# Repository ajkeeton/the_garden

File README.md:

**Garden of the Wads**

Animation states:

0)
    - Glow or pulse near sensors. Occasional LED tracer
    - Wadsworth sighs
    - Venus closed

1)
    - *The initial state on startup*
    - Venus opens
    - The blue blob animation starts
    - Wadsworth breathes slowly, with pauses

2)
    - High energy tracers?
    - More colorful blobs?
    - Fast breathing?

3)
    - Mostly glowing white?
    - Rapid decay to state 2

TODOs:
- Doc PIR sensors and behavior
- The LED patterns are from old projects and need to be refactored
- Garden state updates from the Gardener are currently ignored

*Wadsworth*

*The Venus Hippy Trap*

*The Little Wads*

*Maki's Squishy Thing*

*The Garden server*

*NOTES*

For the Pi 4, need to disable wireless power saving:

```
echo iwconfig wlan0 power off > /etc/rc.local
```

The Arduino core: |The core: https://github.com/earlephilhower/arduino-pico

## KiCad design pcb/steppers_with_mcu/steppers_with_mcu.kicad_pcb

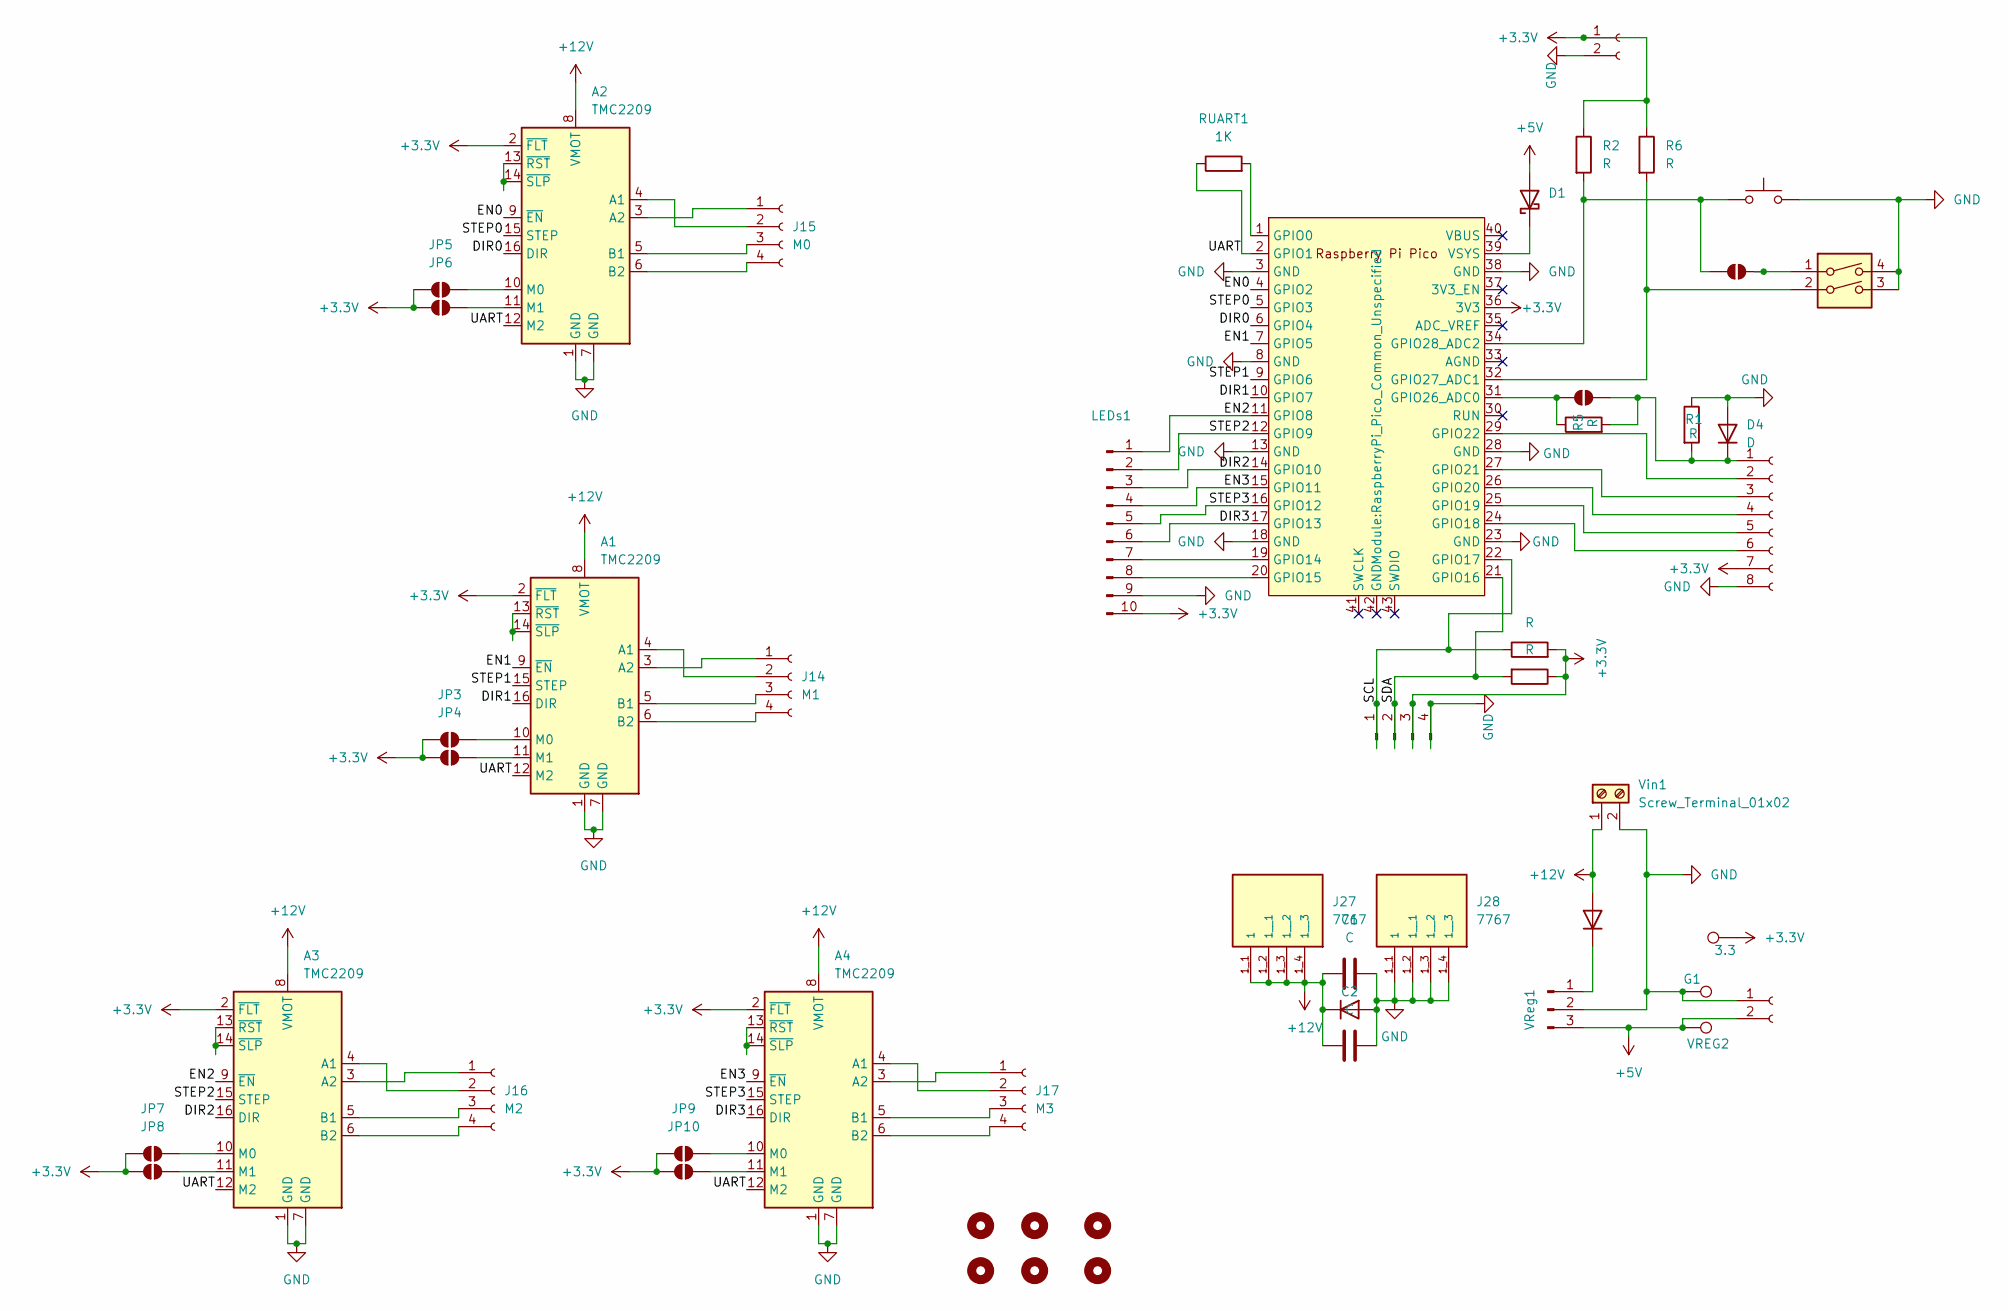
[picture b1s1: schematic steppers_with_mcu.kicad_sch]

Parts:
3.3: TestPoint; TestPoint_Pad_1.5x1.5mm
A1, A2, A3, A4: TMC2209; Pololu_Breakout-16_15.2x20.3mm
C1, C2: C; CP_Radial_D13.0mm_P5.00mm
D1: D_Schottky; D_DO-27_P15.24mm_Horizontal
D2, D3, D4: D; D_A-405_P10.16mm_Horizontal
G1: TestPoint; TestPoint_Pad_1.5x1.5mm
H1, H2, H3, H4, H5, H6: MountingHole; MountingHole_3.2mm_M3_ISO7380_Pad_TopBottom
I2C1: Conn_01x04_Pin; PinHeader_1x04_P2.54mm_Vertical
J2: Conn_01x08_Socket; PinHeader_1x08_P2.54mm_Vertical
J4, J5: Conn_01x02_Socket; PinHeader_1x02_P2.54mm_Vertical
J14: M1; PinHeader_1x04_P2.54mm_Vertical
J15: M0; PinHeader_1x04_P2.54mm_Vertical
J16: M2; PinHeader_1x04_P2.54mm_Vertical
J17: M3; PinHeader_1x04_P2.54mm_Vertical
J27, J28: 7767; KEYSTONE_7767; PARTREV B
JP1, JP2: SolderJumper_2_Open; SolderJumper-2_P1.3mm_Open_RoundedPad1.0x1.5mm
JP3, JP4, JP5, JP6, JP7, JP8, JP9, JP10: SolderJumper_2_Open; SolderJumper-2_P1.3mm_Open_Pad1.0x1.5mm
LEDs1: Conn_01x10_Pin; PinHeader_1x10_P2.54mm_Vertical
R1, R2, R3, R4, R5, R6: R; 1206
RUART1: 1K; 1206
SW1: SW_Push; SW_PUSH_6mm
SW2: SW_DIP_x02; SW_DIP_SPSTx02_Slide_6.7x6.64mm_W7.62mm_P2.54mm_LowProfile
U1: Pico; RaspberryPi_Pico_Common_Unspecified
VREG2: TestPoint; TestPoint_Pad_1.5x1.5mm
VReg1: Conn_01x03_Pin; PinHeader_1x03_P2.54mm_Vertical
Vin1: Screw_Terminal_01x02; TerminalBlock_Phoenix_MKDS-1,5-2_1x02_P5.00mm_Horizontal

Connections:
+3.3V: 3.3.1, A1.2 (~FLT), A2.2 (~FLT), A3.2 (~FLT), A4.2 (~FLT), I2C1.3, J2.7, J4.1, JP3.1 (A), JP4.1 (A), JP5.1 (A), JP6.1 (A), JP7.1 (A), JP8.1 (A), JP9.1 (A), JP10.1 (A), LEDs1.10, R2.1, R3.1, R4.2, R6.1, U1.36 (3V3)
+5V: D1.2 (A), J5.2, VREG2.1, VReg1.3
+12V: A1.8 (VMOT), A2.8 (VMOT), A3.8 (VMOT), A4.8 (VMOT), C1.1, C2.1, D2.2 (A), D3.1 (K), J27.1_1 (1), J27.1_2 (1__1), J27.1_3 (1__2), J27.1_4 (1__3), Vin1.1
/DIR0: A2.16 (DIR), U1.6 (GPIO4)
/DIR1: A1.16 (DIR), U1.10 (GPIO7)
/DIR2: A3.16 (DIR), LEDs1.3, U1.14 (GPIO10)
/DIR3: A4.16 (DIR), LEDs1.6, U1.17 (GPIO13)
/EN0: A2.9 (~EN), U1.4 (GPIO2)
/EN1: A1.9 (~EN), U1.7 (GPIO5)
/EN2: A3.9 (~EN), LEDs1.1, U1.11 (GPIO8)
/EN3: A4.9 (~EN), LEDs1.4, U1.15 (GPIO11)
/SCL: I2C1.1, R4.1, U1.22 (GPIO17)
/SDA: I2C1.2, R3.2, U1.21 (GPIO16)
/STEP0: A2.15 (STEP), U1.5 (GPIO3)
/STEP1: A1.15 (STEP), U1.9 (GPIO6)
/STEP2: A3.15 (STEP), LEDs1.2, U1.12 (GPIO9)
/STEP3: A4.15 (STEP), LEDs1.5, U1.16 (GPIO12)
/UART: A1.12 (M2), A2.12 (M2), A3.12 (M2), A4.12 (M2), RUART1.1, U1.2 (GPIO1)
GND: A1.1 (GND), A1.7 (GND), A2.1 (GND), A2.7 (GND), A3.1 (GND), A3.7 (GND), A4.1 (GND), A4.7 (GND), C1.2, C2.2, D3.2 (A), D4.2 (A), G1.1, I2C1.4, J2.8, J4.2, J5.1, J28.1_1 (1), J28.1_2 (1__1), J28.1_3 (1__2), J28.1_4 (1__3), LEDs1.9, R1.1, SW1.2, SW2.3, SW2.4, U1.3 (GND), U1.8 (GND), U1.13 (GND), U1.18 (GND), U1.23 (GND), U1.28 (GND), U1.38 (GND), VReg1.2, Vin1.2; also elsewhere on the board
unnamed: A1.4 (A1), J14.2
unnamed: A1.3 (A2), J14.1
unnamed: A1.5 (B1), J14.3
unnamed: A1.6 (B2), J14.4
unnamed: A1.10 (M0), JP3.2 (B)
unnamed: A1.11 (M1), JP4.2 (B)
unnamed: A1.13 (~RST), A1.14 (~SLP)
unnamed: A2.4 (A1), J15.2
unnamed: A2.3 (A2), J15.1
unnamed: A2.5 (B1), J15.3
unnamed: A2.6 (B2), J15.4
unnamed: A2.10 (M0), JP5.2 (B)
unnamed: A2.11 (M1), JP6.2 (B)
unnamed: A2.13 (~RST), A2.14 (~SLP)
unnamed: A3.4 (A1), J16.2
unnamed: A3.3 (A2), J16.1
unnamed: A3.5 (B1), J16.3
unnamed: A3.6 (B2), J16.4
unnamed: A3.10 (M0), JP7.2 (B)
unnamed: A3.11 (M1), JP8.2 (B)
unnamed: A3.13 (~RST), A3.14 (~SLP)
unnamed: A4.4 (A1), J17.2
unnamed: A4.3 (A2), J17.1
unnamed: A4.5 (B1), J17.3
unnamed: A4.6 (B2), J17.4
unnamed: A4.10 (M0), JP9.2 (B)
unnamed: A4.11 (M1), JP10.2 (B)
unnamed: A4.13 (~RST), A4.14 (~SLP)
unnamed: D1.1 (K), U1.39 (VSYS)
unnamed: D2.1 (K), VReg1.1
unnamed: D4.1 (K), J2.1, JP2.1 (A), R1.2, R5.2
unnamed: J2.2, U1.29 (GPIO22)
unnamed: J2.3, U1.27 (GPIO21)
unnamed: J2.4, U1.26 (GPIO20)
unnamed: J2.5, U1.25 (GPIO19)
unnamed: J2.6, U1.24 (GPIO18)
unnamed: JP1.1 (A), SW2.1
unnamed: JP1.2 (B), R2.2, SW1.1, U1.34 (GPIO28_ADC2)
unnamed: JP2.2 (B), R5.1, U1.31 (GPIO26_ADC0)
unnamed: LEDs1.7, U1.19 (GPIO14)
unnamed: LEDs1.8, U1.20 (GPIO15)
unnamed: RUART1.2, U1.1 (GPIO0)
unnamed: R6.2, SW2.2, U1.32 (GPIO27_ADC1)

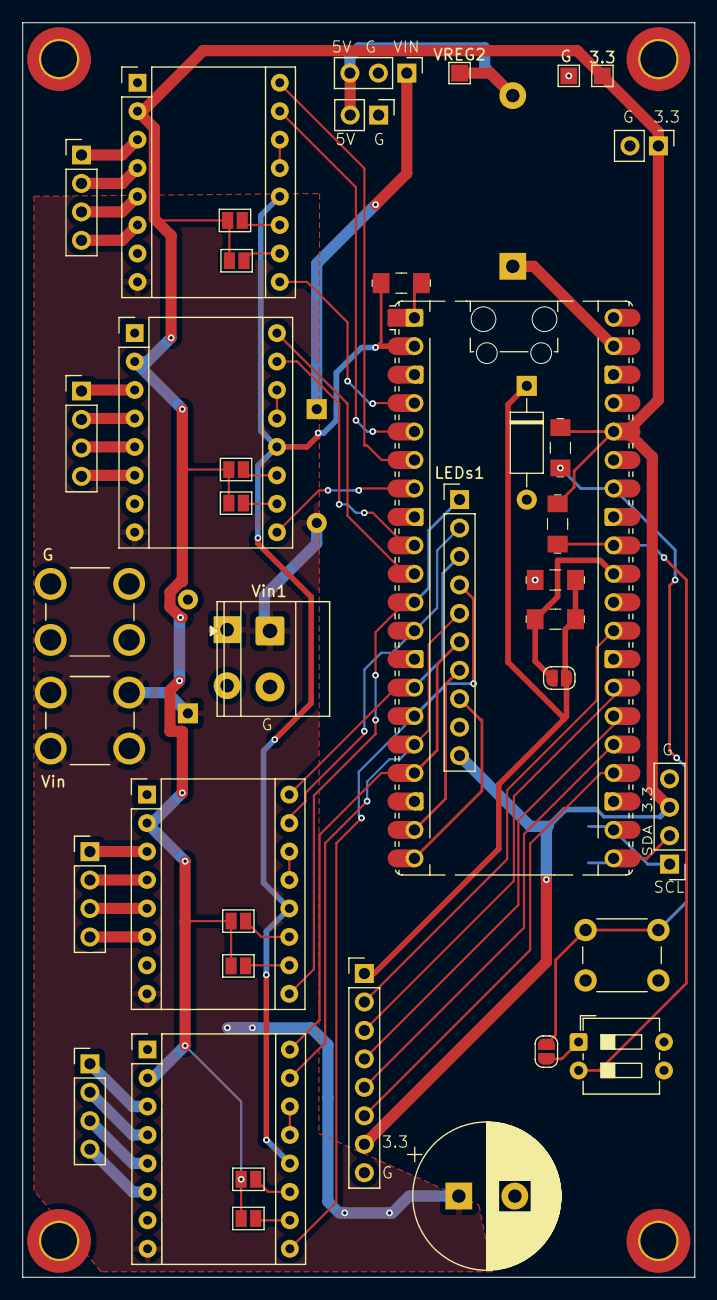
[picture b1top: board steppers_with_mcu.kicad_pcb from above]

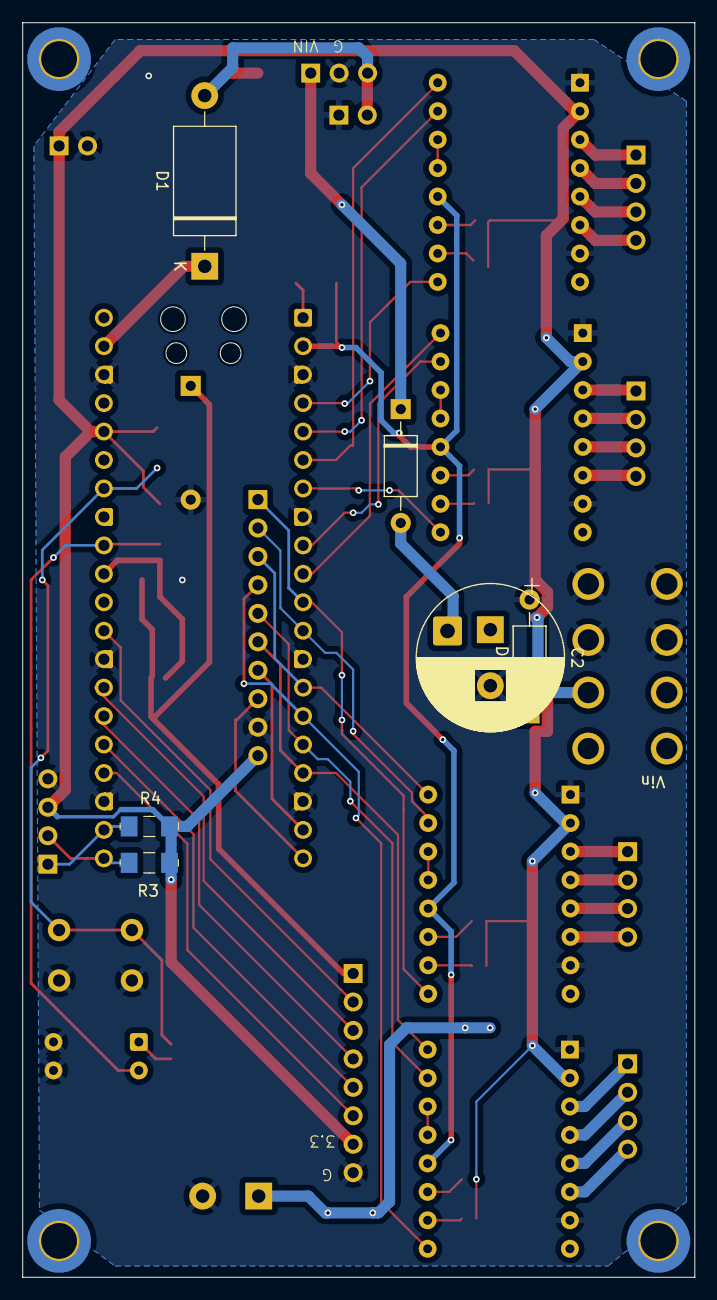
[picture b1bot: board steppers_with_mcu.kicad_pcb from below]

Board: 2 copper layers, 60.0 x 112.0 mm, 50 parts (6 on the bottom side), 62 nets.

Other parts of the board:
G: TestPoint; TestPoint_Pad_1.5x1.5mm

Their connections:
GND: G.1; also elsewhere on the board

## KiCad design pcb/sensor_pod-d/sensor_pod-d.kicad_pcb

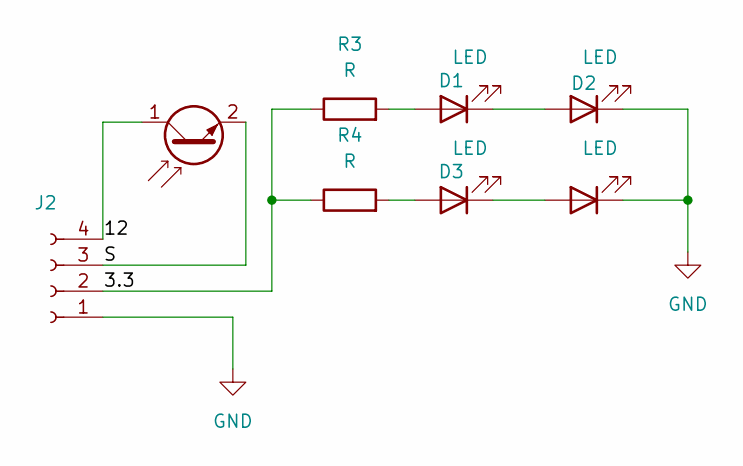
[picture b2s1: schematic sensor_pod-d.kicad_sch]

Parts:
D1, D2, D3, D4: LED; PinHeader_1x02_P2.54mm_Vertical
J2: Conn_01x04_Socket; PinHeader_1x04_P2.54mm_Vertical
Q2: Q_Photo_NPN; PinHeader_1x02_P2.54mm_Vertical
R3, R4: R; 1206

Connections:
/3.3: J2.2, R3.1, R4.1
/12: J2.4, Q2.1 (C)
/S: J2.3, Q2.2 (E)
GND: D2.1 (K), D4.1 (K), J2.1
unnamed: D1.2 (A), R3.2
unnamed: D1.1 (K), D2.2 (A)
unnamed: D3.2 (A), R4.2
unnamed: D3.1 (K), D4.2 (A)

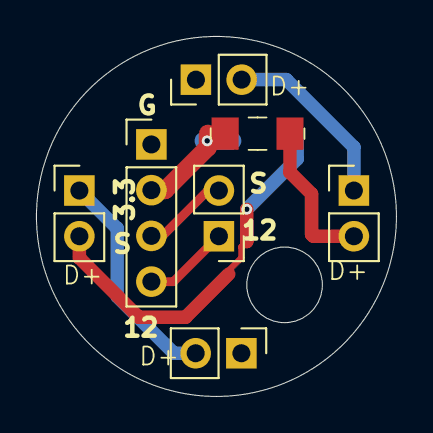
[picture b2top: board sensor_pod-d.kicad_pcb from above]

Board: 2 copper layers, 20.0 x 20.0 mm, 8 parts (1 on the bottom side), 8 nets.

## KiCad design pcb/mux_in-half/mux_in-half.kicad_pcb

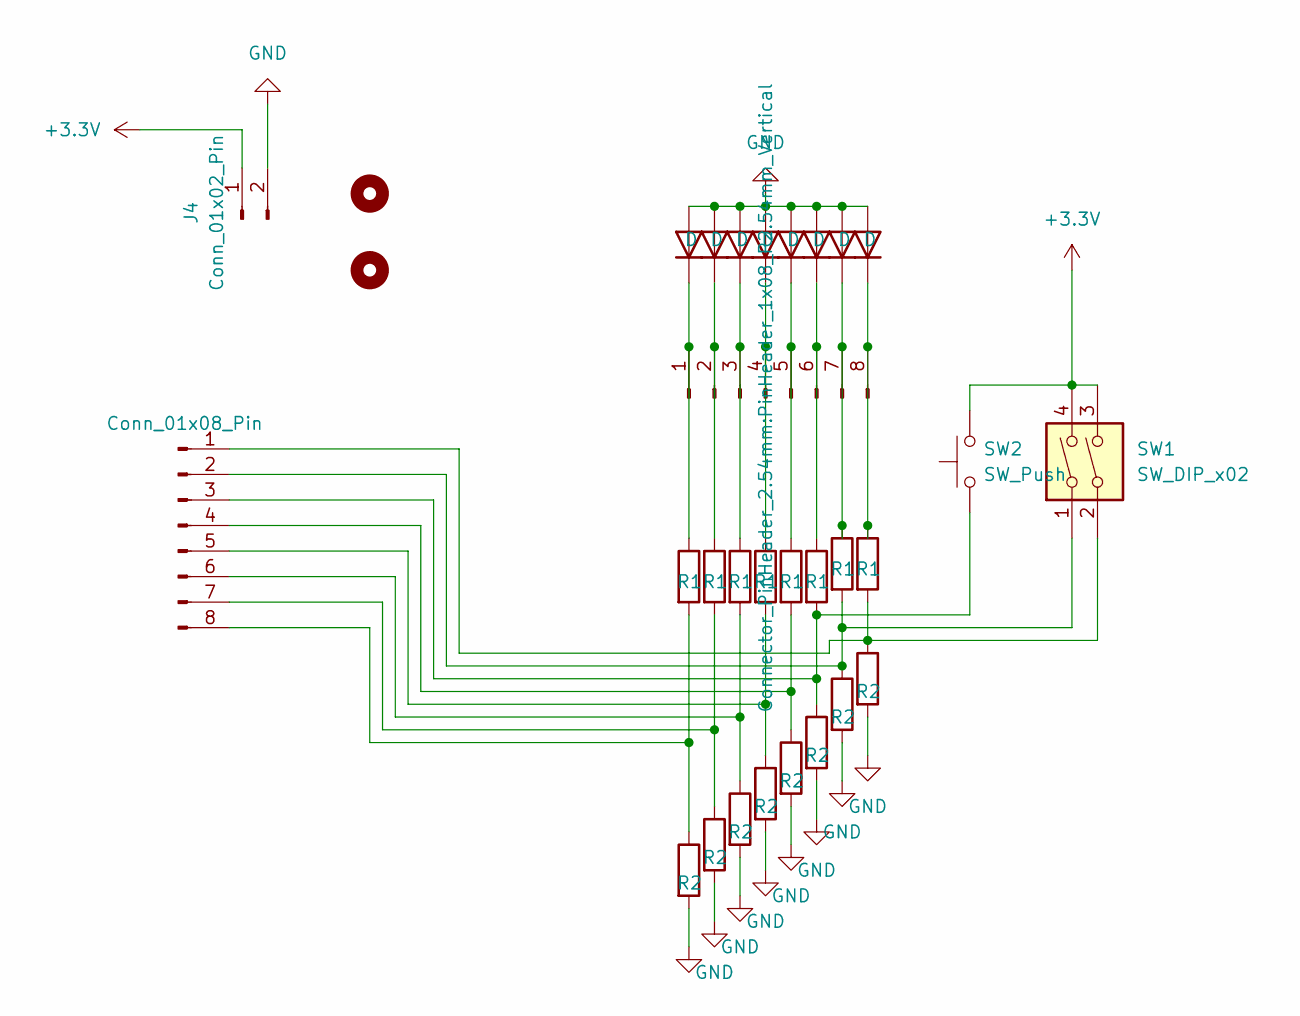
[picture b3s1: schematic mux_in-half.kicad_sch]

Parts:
D9, D10, D11, D12, D13, D14, D15, D16: D; D_SMF
H1, H2: MountingHole; MountingHole_2.5mm_Pad
J1, J2: Conn_01x08_Pin; PinHeader_1x08_P2.54mm_Vertical
J4: Conn_01x02_Pin; PinHeader_1x02_P2.54mm_Vertical
R17, R19, R21, R23, R25, R27, R29, R31: R1; 1206
R18, R20, R22, R24, R26, R28, R30, R32: R2; 1206
SW1: SW_DIP_x02; SW_DIP_SPSTx02_Slide_6.7x6.64mm_W7.62mm_P2.54mm_LowProfile
SW2: SW_Push; SW_PUSH_6mm

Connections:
+3.3V: J4.1, SW1.3, SW1.4, SW2.2
GND: D9.2 (A), D10.2 (A), D11.2 (A), D12.2 (A), D13.2 (A), D14.2 (A), D15.2 (A), D16.2 (A), J4.2, R18.2, R20.2, R22.2, R24.2, R26.2, R28.2, R30.2, R32.2
unnamed: D9.1 (K), J2.1, R17.1
unnamed: D10.1 (K), J2.2, R19.1
unnamed: D11.1 (K), J2.3, R21.1
unnamed: D12.1 (K), J2.4, R23.1
unnamed: D13.1 (K), J2.5, R25.1
unnamed: D14.1 (K), J2.6, R27.1
unnamed: D15.1 (K), J2.7, R29.1
unnamed: D16.1 (K), J2.8, R31.1
unnamed: J1.1, R31.2, R32.1, SW1.2
unnamed: J1.2, R29.2, R30.1, SW1.1
unnamed: J1.3, R27.2, R28.1, SW2.1
unnamed: J1.4, R25.2, R26.1
unnamed: J1.5, R23.2, R24.1
unnamed: J1.6, R21.2, R22.1
unnamed: J1.7, R19.2, R20.1
unnamed: J1.8, R17.2, R18.1

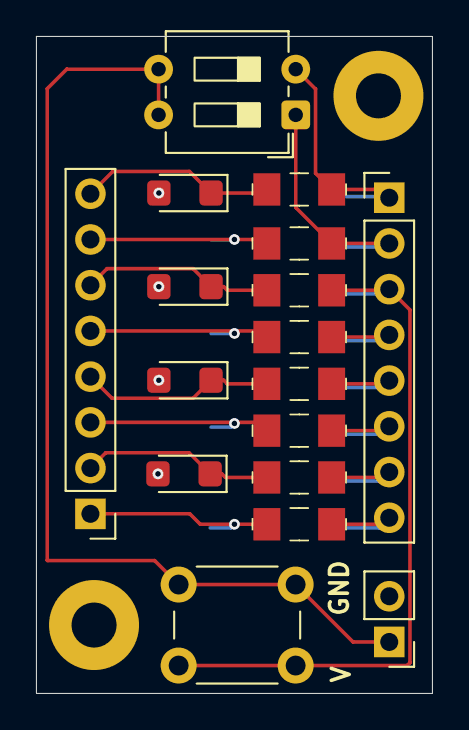
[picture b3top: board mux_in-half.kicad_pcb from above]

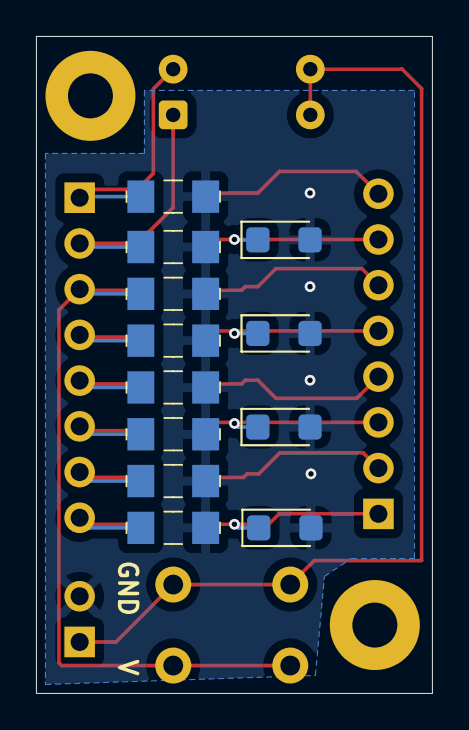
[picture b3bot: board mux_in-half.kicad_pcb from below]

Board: 2 copper layers, 22.0 x 36.5 mm, 31 parts (12 on the bottom side), 18 nets.

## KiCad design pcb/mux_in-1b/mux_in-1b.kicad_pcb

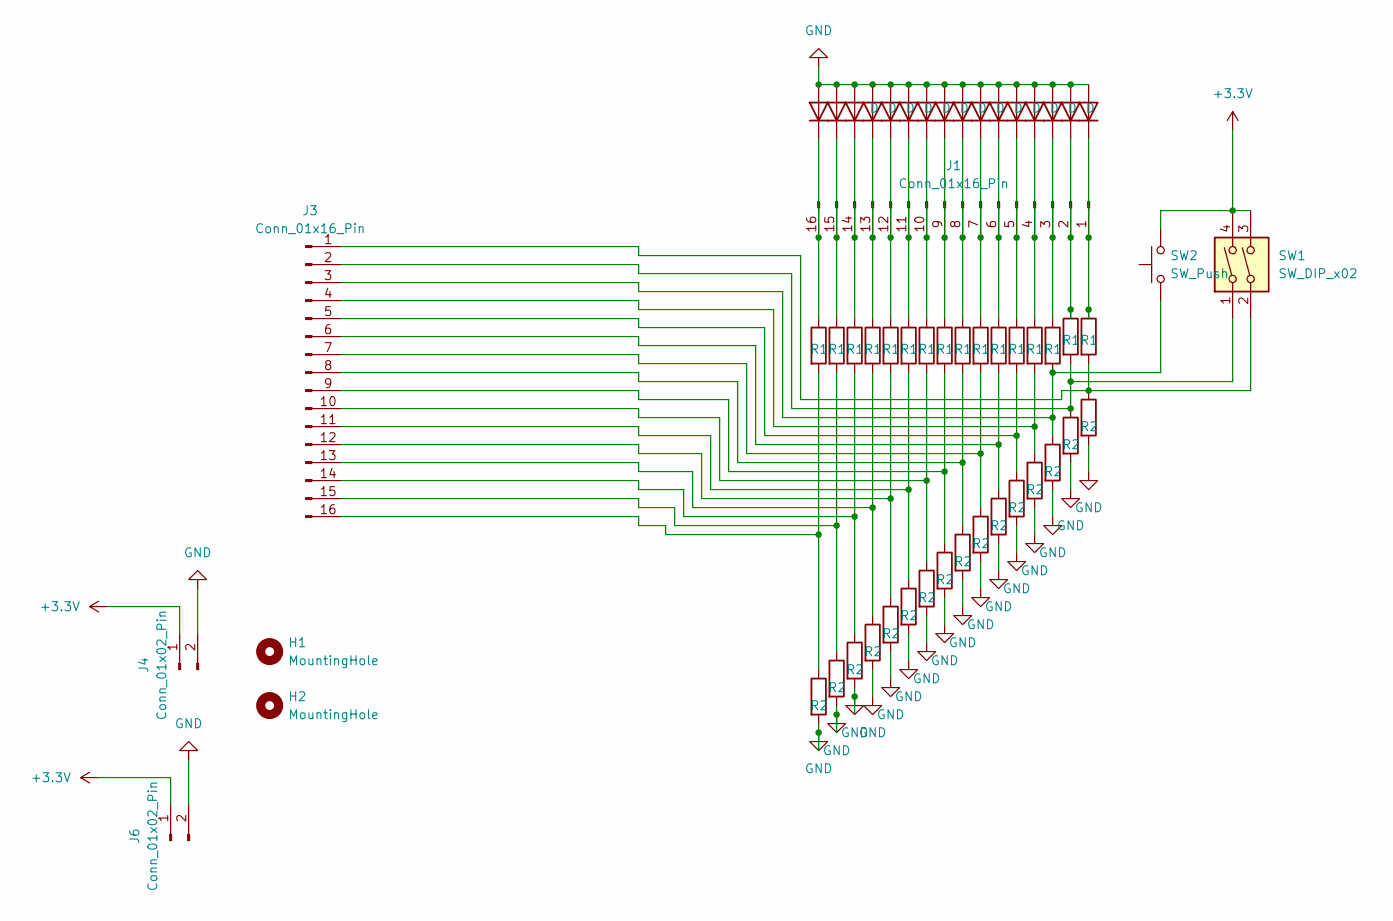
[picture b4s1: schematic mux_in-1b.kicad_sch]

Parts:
D1, D2, D3, D4, D5, D6, D7, D8, D9, D10, D11, D12, D13, D14, D15, D16: D; D_DO-41_SOD81_P7.62mm_Horizontal
H1, H2: MountingHole; MountingHole_2.5mm_Pad
J1, J3: Conn_01x16_Pin; PinSocket_1x16_P2.54mm_Vertical
J4, J6: Conn_01x02_Pin; PinHeader_1x02_P2.54mm_Vertical
R1, R3, R5, R7, R9, R11, R13, R15, R17, R19, R21, R23, R25, R27, R29, R31: R1; 1206
R2, R4, R6, R8, R10, R12, R14, R16, R18, R20, R22, R24, R26, R28, R30, R32: R2; 1206
SW1: SW_DIP_x02; SW_DIP_SPSTx02_Slide_6.7x6.64mm_W7.62mm_P2.54mm_LowProfile
SW2: SW_Push; SW_PUSH_6mm

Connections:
+3.3V: J4.1, J6.1, SW1.3, SW1.4, SW2.2
GND: D1.2 (A), D2.2 (A), D3.2 (A), D4.2 (A), D5.2 (A), D6.2 (A), D7.2 (A), D8.2 (A), D9.2 (A), D10.2 (A), D11.2 (A), D12.2 (A), D13.2 (A), D14.2 (A), D15.2 (A), D16.2 (A), J4.2, J6.2, R2.2, R4.2, R6.2, R8.2, R10.2, R12.2, R14.2, R16.2, R18.2, R20.2, R22.2, R24.2, R26.2, R28.2, R30.2, R32.2
unnamed: D1.1 (K), J1.16, R1.1
unnamed: D2.1 (K), J1.15, R3.1
unnamed: D3.1 (K), J1.14, R5.1
unnamed: D4.1 (K), J1.13, R7.1
unnamed: D5.1 (K), J1.12, R9.1
unnamed: D6.1 (K), J1.11, R11.1
unnamed: D7.1 (K), J1.10, R13.1
unnamed: D8.1 (K), J1.9, R15.1
unnamed: D9.1 (K), J1.8, R17.1
unnamed: D10.1 (K), J1.7, R19.1
unnamed: D11.1 (K), J1.6, R21.1
unnamed: D12.1 (K), J1.5, R23.1
unnamed: D13.1 (K), J1.4, R25.1
unnamed: D14.1 (K), J1.3, R27.1
unnamed: D15.1 (K), J1.2, R29.1
unnamed: D16.1 (K), J1.1, R31.1
unnamed: J3.1, R31.2, R32.1, SW1.2
unnamed: J3.2, R29.2, R30.1, SW1.1
unnamed: J3.3, R27.2, R28.1, SW2.1
unnamed: J3.4, R25.2, R26.1
unnamed: J3.5, R23.2, R24.1
unnamed: J3.6, R21.2, R22.1
unnamed: J3.7, R19.2, R20.1
unnamed: J3.8, R17.2, R18.1
unnamed: J3.9, R15.2, R16.1
unnamed: J3.10, R13.2, R14.1
unnamed: J3.11, R11.2, R12.1
unnamed: J3.12, R9.2, R10.1
unnamed: J3.13, R7.2, R8.1
unnamed: J3.14, R5.2, R6.1
unnamed: J3.15, R3.2, R4.1
unnamed: J3.16, R1.2, R2.1

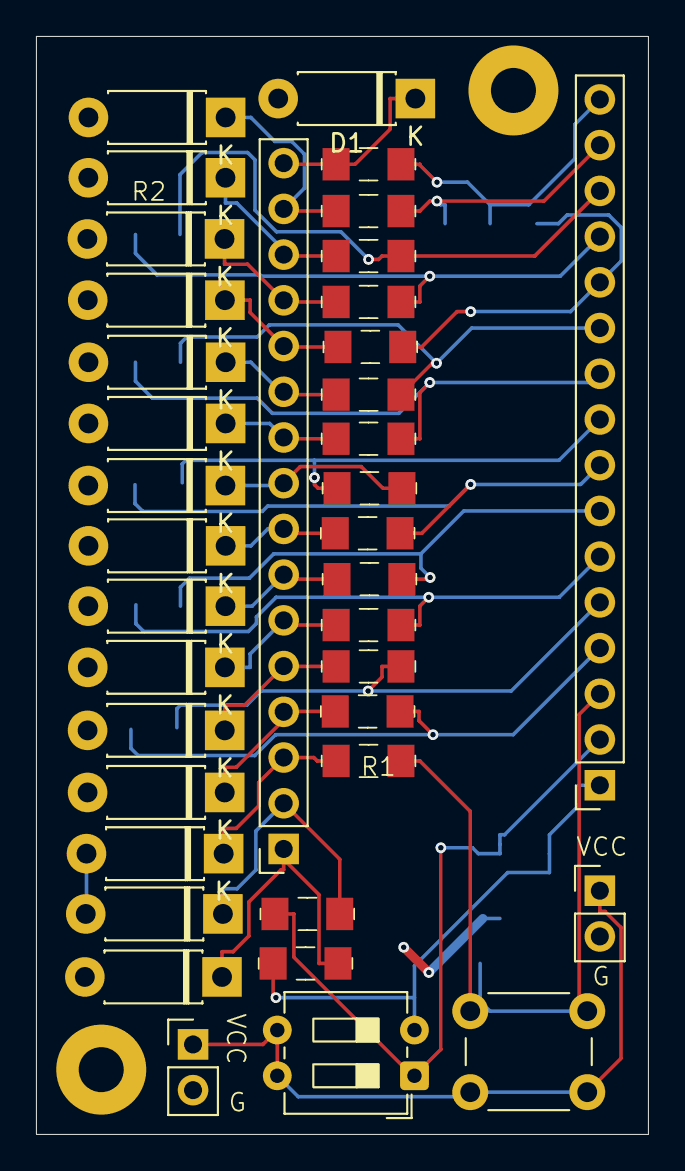
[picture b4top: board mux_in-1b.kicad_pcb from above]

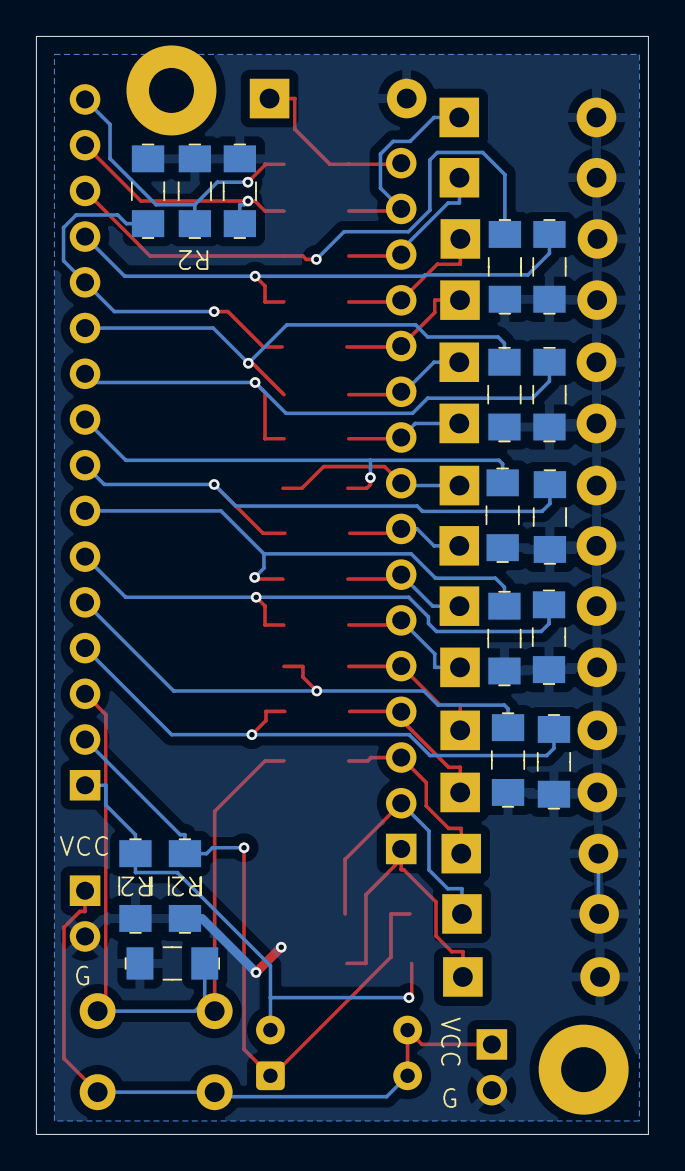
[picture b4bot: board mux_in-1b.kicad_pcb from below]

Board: 2 copper layers, 34.0 x 61.0 mm, 56 parts (16 on the bottom side), 34 nets.

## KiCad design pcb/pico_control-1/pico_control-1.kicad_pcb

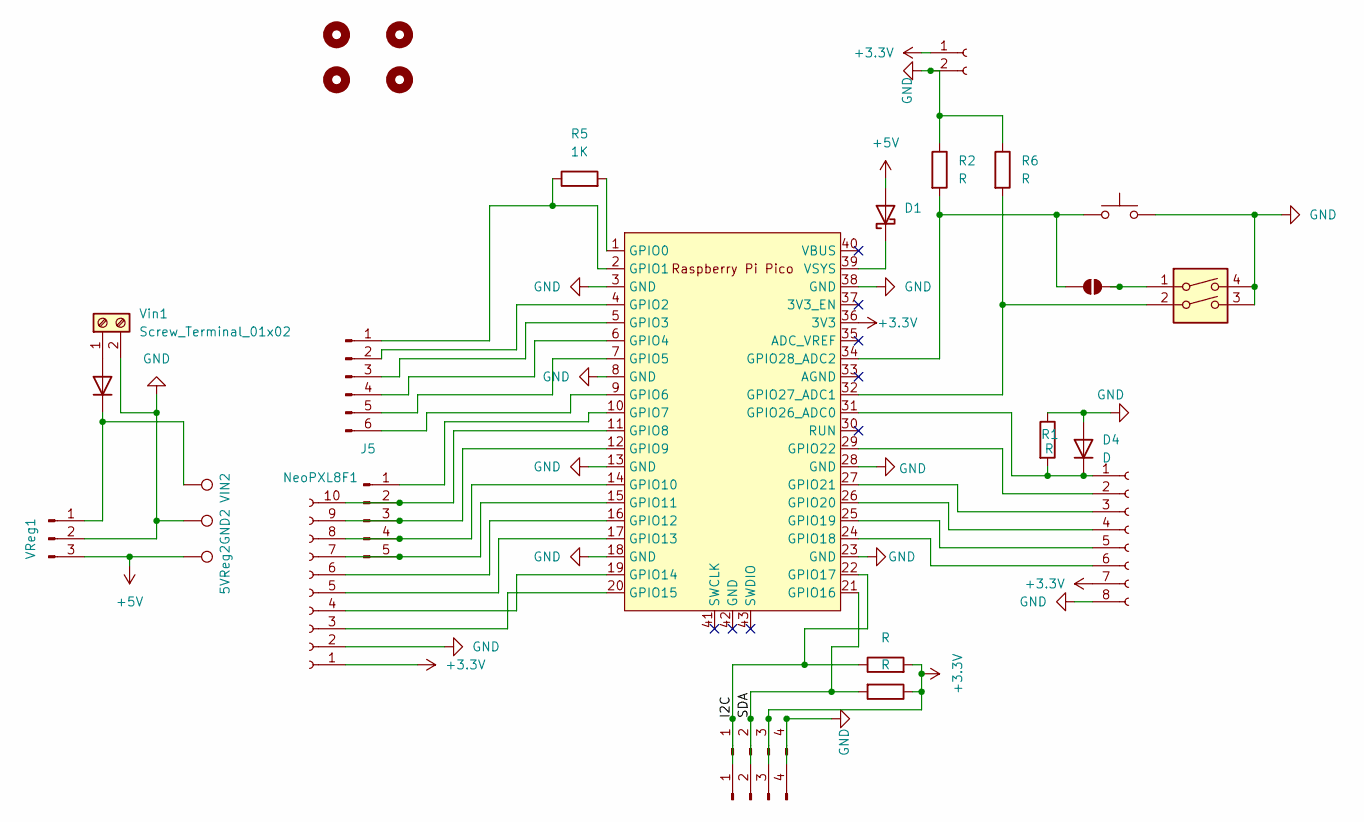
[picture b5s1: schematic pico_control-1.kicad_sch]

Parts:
5VReg2: TestPoint; TestPoint_Pad_1.5x1.5mm
D1: D_Schottky; D_DO-27_P15.24mm_Horizontal
D2, D4: D; D_A-405_P10.16mm_Horizontal
GND2: TestPoint; TestPoint_Pad_1.5x1.5mm
H1, H2, H3, H4: MountingHole; MountingHole_3.2mm_M3
I2C1, I2C2: Conn_01x04_Pin; PinHeader_1x04_P2.54mm_Vertical
J1: Conn_01x06_Pin; PinHeader_1x06_P2.54mm_Vertical
J2: Conn_01x08_Socket; PinHeader_1x08_P2.54mm_Vertical
J4: Conn_01x02_Socket; PinHeader_1x2_P2.54mm
J5: Conn_01x05_Pin; PinHeader_1x05_P2.54mm_Vertical
JP1: SolderJumper_2_Open; SolderJumper-2_P1.3mm_Open_RoundedPad1.0x1.5mm
NeoPXL8F1: Conn_01x10_Socket; PinHeader_1x10_P2.54mm_Vertical
R1, R2, R3, R4, R6: R; 1206
R5: 1K; 1206
SW1: SW_Push; SW_PUSH_6mm
SW2: SW_DIP_x02; SW_DIP_SPSTx02_Slide_6.7x6.64mm_W7.62mm_P2.54mm_LowProfile
U1: Pico; RaspberryPi_Pico_Common_Unspecified
VIN2: TestPoint; TestPoint_Pad_1.5x1.5mm
VReg1: Conn_01x03_Pin; PinHeader_1x03_P2.54mm_Vertical
Vin1: Screw_Terminal_01x02; TerminalBlock_Phoenix_MKDS-1,5-2_1x02_P5.00mm_Horizontal

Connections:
+3.3V: I2C1.3, I2C2.3, J2.7, J4.1, NeoPXL8F1.1, R3.1, R4.2, U1.36 (3V3)
+5V: 5VReg2.1, D1.2 (A), VReg1.3; also elsewhere on the board
/I2C: I2C1.1, I2C2.1, R4.1, U1.22 (GPIO17)
/SDA: I2C1.2, I2C2.2, R3.2, U1.21 (GPIO16)
GND: D4.2 (A), GND2.1, I2C1.4, I2C2.4, J2.8, J4.2, NeoPXL8F1.2, R1.1, R2.1, R6.1, SW1.2, SW2.3, SW2.4, U1.3 (GND), U1.8 (GND), U1.13 (GND), U1.18 (GND), U1.23 (GND), U1.28 (GND), U1.38 (GND), VReg1.2, Vin1.2; also elsewhere on the board
unnamed: D1.1 (K), U1.39 (VSYS)
unnamed: D2.2 (A), Vin1.1
unnamed: D2.1 (K), VIN2.1, VReg1.1
unnamed: D4.1 (K), J2.1, R1.2, U1.31 (GPIO26_ADC0)
unnamed: J1.1, R5.1, U1.2 (GPIO1)
unnamed: J1.2, U1.4 (GPIO2)
unnamed: J1.3, U1.5 (GPIO3)
unnamed: J1.4, U1.6 (GPIO4)
unnamed: J1.5, U1.7 (GPIO5)
unnamed: J1.6, U1.9 (GPIO6)
unnamed: J2.2, U1.29 (GPIO22)
unnamed: J2.3, U1.27 (GPIO21)
unnamed: J2.4, U1.26 (GPIO20)
unnamed: J2.5, U1.25 (GPIO19)
unnamed: J2.6, U1.24 (GPIO18)
unnamed: J5.1, U1.10 (GPIO7)
unnamed: J5.2, NeoPXL8F1.10, U1.11 (GPIO8)
unnamed: J5.3, NeoPXL8F1.9, U1.12 (GPIO9)
unnamed: J5.4, NeoPXL8F1.8, U1.14 (GPIO10)
unnamed: J5.5, NeoPXL8F1.7, U1.15 (GPIO11)
unnamed: JP1.1 (A), SW2.1
unnamed: JP1.2 (B), R2.2, SW1.1, U1.34 (GPIO28_ADC2)
unnamed: NeoPXL8F1.3, U1.20 (GPIO15)
unnamed: NeoPXL8F1.4, U1.19 (GPIO14)
unnamed: NeoPXL8F1.5, U1.17 (GPIO13)
unnamed: NeoPXL8F1.6, U1.16 (GPIO12)
unnamed: R5.2, U1.1 (GPIO0)
unnamed: R6.2, SW2.2, U1.32 (GPIO27_ADC1)

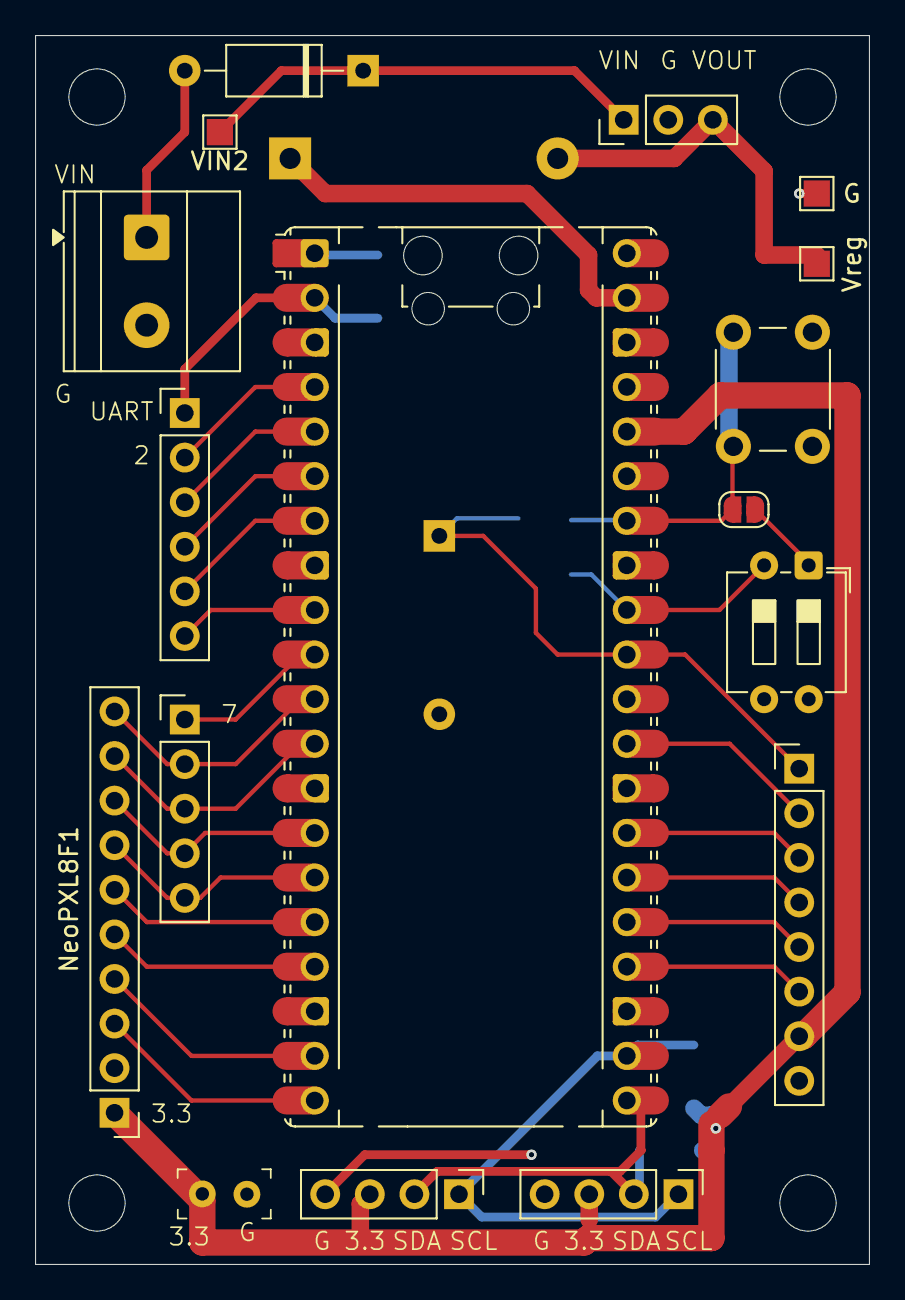
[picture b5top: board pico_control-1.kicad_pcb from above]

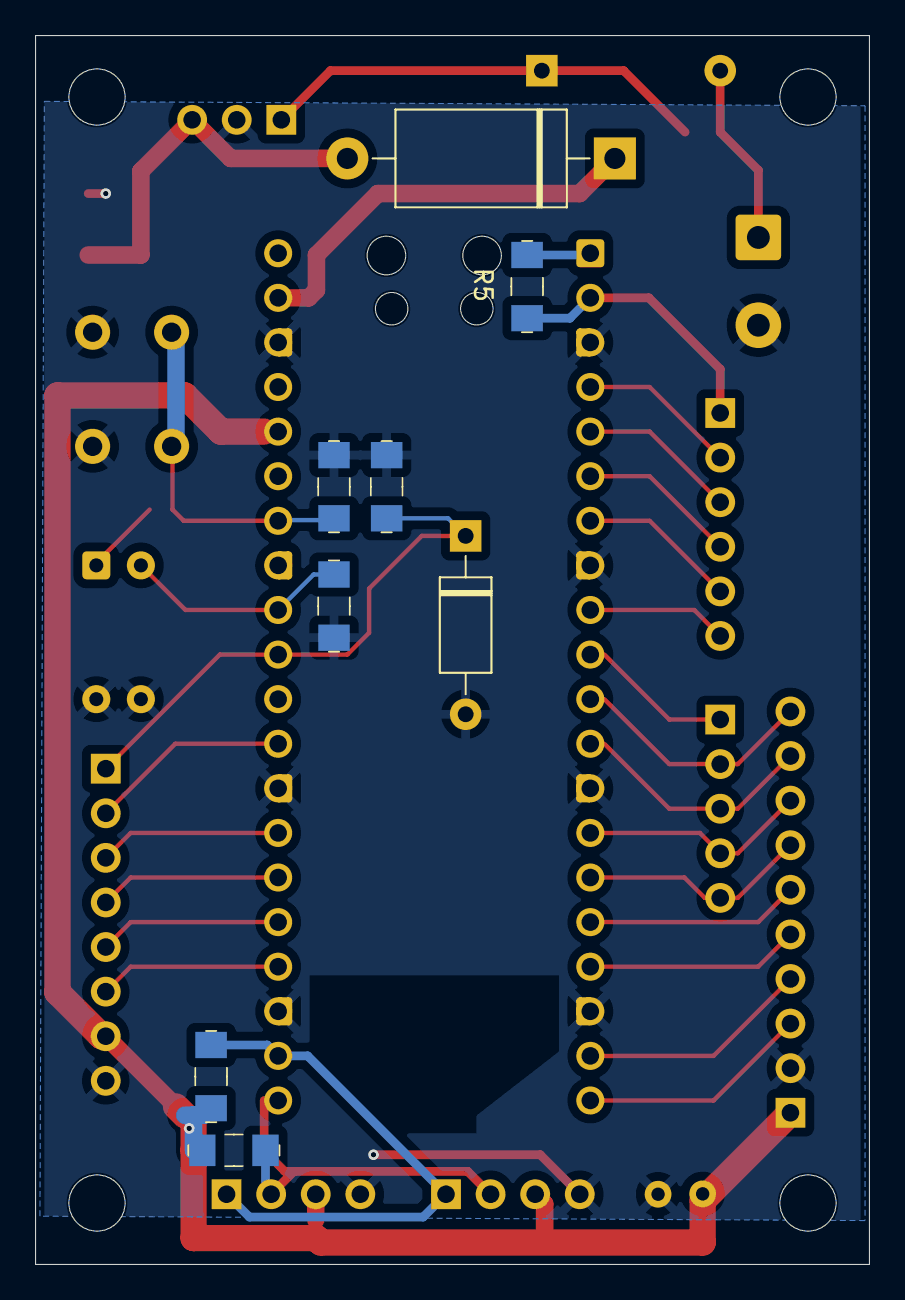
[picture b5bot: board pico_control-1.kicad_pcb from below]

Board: 2 copper layers, 47.5 x 70.0 mm, 29 parts (8 on the bottom side), 33 nets.

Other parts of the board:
G: TestPoint; TestPoint_Pad_1.5x1.5mm
Vreg: TestPoint; TestPoint_Pad_1.5x1.5mm

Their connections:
+5V: Vreg.1; also elsewhere on the board
GND: G.1; also elsewhere on the board

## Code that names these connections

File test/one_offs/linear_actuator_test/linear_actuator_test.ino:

const int PWM1 = 0;
const int DIR1 = 1;
const int DIR2 = 2;

const int PWM2 = 3;
const int DIR3 = 4;
const int DIR4 = 5;

const int STICK1 = A0;
const int STICK2 = A1;

//const int POS1 = A2;
//const int POS2 = A3;

void setup() {
  // put your setup code here, to run once:
  analogWriteFreq(8000);

  pinMode(PWM1, OUTPUT);
  pinMode(DIR1, OUTPUT);
  pinMode(DIR2, OUTPUT);
  pinMode(PWM2, OUTPUT);
  pinMode(DIR3, OUTPUT);
  pinMode(DIR4, OUTPUT);
  
  pinMode(LED_BUILTIN, OUTPUT);
  digitalWrite(DIR1, 0);
  digitalWrite(DIR2, 0);
  digitalWrite(DIR3, 0);
  digitalWrite(DIR4, 0);

  Serial.begin(9600);
  delay(100);
  Serial.println("Starting...");
}

void set_forward(const uint16_t pin1, const uint16_t pin2) {
  digitalWrite(pin1, 1);
  digitalWrite(pin2, 0);
}

void set_backward(const uint16_t pin1, const uint16_t pin2) {
  digitalWrite(pin1, 0);
  digitalWrite(pin2, 1);
}

uint16_t get_pos(uint8_t pin) {
  return map(analogRead(pin), 0, 1024, 0, 100);
}

void _loop(const uint16_t stick, const uint16_t pwm, const uint16_t dir1, const uint16_t dir2) {
  // put your main code here, to run repeatedly:
  //static int newx = 0, lastx = 0;
  int x = analogRead(stick);
  // XXX necessary per docs to have 100ms delay when changing directions
  static bool was_forward = false;
  
  if(abs(x - 512) < 50) {
    analogWrite(pwm, 0);
    digitalWrite(LED_BUILTIN, 0);
    return;
  }

  digitalWrite(LED_BUILTIN, 1);

 //newx = x - lastx;
 // if(abs(newx) > 10) {
 //   lastx = x;
 // }

  if(x > 512) {
    if(!was_forward) {
      // XXX necessary per docs to have 100ms delay when changing directions
      delay(150);
    }
    was_forward = true;
    set_forward(dir1, dir2);
  }
  else {
    if(was_forward) {
      // XXX necessary per docs to have 100ms delay when changing directions
      delay(150);
    }
    was_forward = false;
    set_backward(dir1, dir2);
  }

  uint16_t speed = map(abs(x-512), 0, 512, 0, 255);
  Serial.printf("%d: %d - %d, %d\n", pwm, speed, x, was_forward);
  analogWrite(pwm, speed);
}

void loop() {
  _loop(STICK1, PWM1, DIR1, DIR2);
}

void loop1() {
  _loop(STICK2, PWM2, DIR3, DIR4);
}

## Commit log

2025-03-17 Adding functionality to Venus
2025-03-22 More goods
2025-03-26 Now relying on one limit switch. Rudimentary acceleration
2025-03-27 State machine taking shape
2025-04-06 Platform.ini and main.cpp for new eadsworth setup
2025-04-06 Acceleration slightly better. Saving progress. Also: new PCBs
2025-04-08 Acceleration usable. Working on more states and syncing up how fingers close
2025-04-10 Better states
2025-04-12 Steps towards WiFi. Note: Venus hardcoded to sweep
2025-04-14 Now with wifi, leds, and fixed integer overflow
2025-04-14 Adding the 'mycelial' server, a state and command hub accessible over WiFi
2025-04-14 Some cleaning and fleshing out comms
2025-04-15 Improved behaviors and timing
2025-04-15 Adding old Wadsworth code
2025-04-16 New PCB
2025-04-16 Old code working with some hacked in changes. Time to refactor
2025-04-18 Thoroughly refactored the old Wadsworth code. This is the way
2025-04-18 Now doing the sensor pulse. Reorg'ed. Possibly non-blocking wifi
2025-04-19 Adding msg queue. Now sending pulses to The Gardener to forward to other nodes
2025-04-22 Improved wifi. Pulses better. No more LeaMDNS
2025-05-02 Starting refactor of the old pattern code. Adding support for PIRs
2025-05-02 Protocol updates for PIR support
2025-05-02 New sensor board
2025-05-02 Updates for PIR state messaging
2025-05-04 Gardener now handling delayed messages for fun timing
2025-05-04 PCB fixes and adjustments
2025-05-04 Updates for delayed messages
2025-05-04 Adding PoC code for communicating with the gardener
2025-05-06 Move mechnical code over
2025-05-07 Better comms with Gardener. Mostly fixes. Some cleanup.
2025-05-30 Almost Apo ready. About to refactor/reorg for Venus
2025-05-30 Reorg for Venus to use same LED animations
2025-06-01 latest changes for Wadsworth-mechanical
2025-06-01 LED stuff for Venus
2025-06-03 Adding sleepy_time and better score tracking
2025-06-17 Latest venus with sensor changes
2025-06-18 Adjusting speeds
2025-06-18 Adding new PCB
2025-07-15 Fixing pause_min
